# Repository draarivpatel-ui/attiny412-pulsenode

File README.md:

# ATtiny412 PulseNode

A compact 2-layer node built around the 8-pin ATtiny412-SSNR (SOIC-8) microcontroller: an ambient-light-driven PWM LED with a button, a status LED, and a piezo click. Designed in KiCad 8.

**Live inspector:** `index.html` (served by GitHub Pages) shows the board in 3D and 2D, the net routing status, and every download. It is generated from the KiCad file, so its numbers always match the board.

## Current state

- The `.kicad_pcb` board is `36 x 26 x 1.6 mm`, 2 copper layers, and carries 4 placed footprints: `U1` (ATtiny412-SSNR), `C1` (100nF 0805), `D1` (amber LED, 0805) and `J1` (1x03 UPDI header).
- `bom.csv` lists 12 parts (also resistors, a status LED, a phototransistor, a tactile switch and a piezo). Those are not placed on the board yet, so four MCU pins (`PA6`, `PA7`, `PA1`, `PA2`) reach no other pad.
- 3 connections on `+5V` and `GND` are still unrouted. The Gerbers in `gerbers/` match the board as it stands today and are not a finished order package.

## Hardware Overview

- **Microcontroller** ATtiny412-SSNR (SOIC-8, UPDI single-wire programming on `PA0`, header `J1`)
- **Power** 5.0V and GND, with a 100nF 0805 ceramic capacitor (`C1`) across `VDD` (pin 1) and `GND` (pin 8)
- **Pin map** (from `firmware/attiny412_pulsenode.ino`) pin 2 `PA6` piezo, pin 3 `PA7` LDR input, pin 4 `PA1` button, pin 5 `PA2` status LED, pin 6 `PA0` UPDI, pin 7 `PA3` PWM LED
- **Board Dimensions** `36 x 26 mm`, 1.6 mm thick, as measured from the KiCad outline

## Repository Structure

- `attiny412-pulsenode.kicad_pro`, `attiny412-pulsenode.kicad_sch`, `attiny412-pulsenode.kicad_pcb` KiCad 8 project, schematic and PCB (copies also in `pcb/`)
- `gerbers/` Gerber layers and Excellon drill file for the current board, plus `attiny412-pulsenode-gerbers.zip`
- `bom.csv` Bill of Materials with LCSC, DigiKey and Microchip part numbers
- `firmware/attiny412_pulsenode.ino` megaTinyCore sketch: the button cycles three modes (ambient auto-dimming, a breathing pulse, a blinking beacon) with a piezo click
- `cad/` 3D assembly (`.step`, `.FCStd`) of the board with envelope bodies for the parts
- `assets/`, `tools/`, `index.html` the inspector page and the script (`tools/build_assets.py`) that regenerates its data, STL, STEP, Gerbers and hashes from the KiCad file

## Interactive Schematic & PCB Viewer

Inspect the schematic and PCB online via KiCanvas:
`https://kicanvas.org/?github=https%3A%2F%2Fgithub.com%2Fdraarivpatel-ui%2Fattiny412-pulsenode`

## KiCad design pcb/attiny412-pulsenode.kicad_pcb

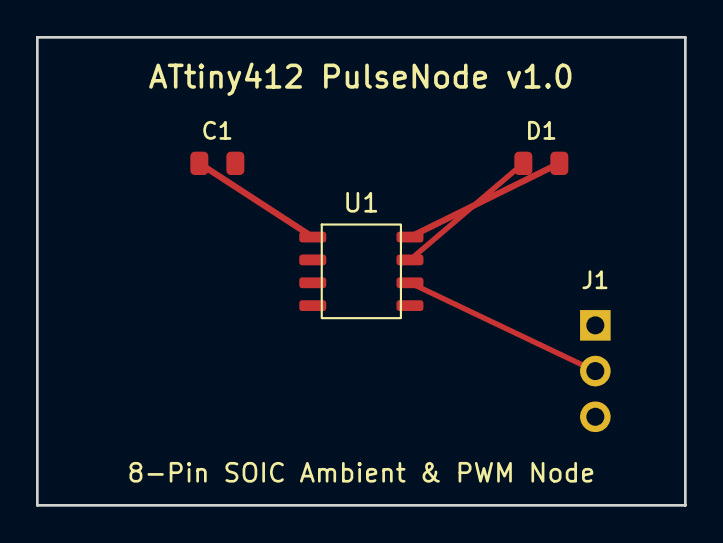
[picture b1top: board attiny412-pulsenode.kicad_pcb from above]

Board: 2 copper layers, 36.0 x 26.0 mm, 4 parts (0 on the bottom side), 4 nets.

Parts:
C1: 100nF; C_0805_2012Metric
D1: PWM_AMBER; LED_0805_2012Metric
J1: UPDI_HDR; PinHeader_1x03_P2.54mm_Vertical
U1: ATtiny412-SSNR; SOIC-8_3.9x4.9mm_P1.27mm

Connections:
+5V: C1.1, J1.1, U1.1
GND: C1.2, D1.2, J1.3, U1.8
PA0_UPDI: J1.2, U1.6
PA3_PWM: D1.1, U1.7
